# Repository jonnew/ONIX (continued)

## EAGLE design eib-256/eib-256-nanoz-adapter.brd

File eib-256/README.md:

# eib-256
256-channel electrode interface board (EIB) with electrical and optical
stimulation. Designed for large animal (e.g. rat) tetrode electrophysiology.
Compatible with [headstage-256](../headstage-256/) and large shuttle-drives.

## Gerber Files
{% include gerber_layers.md %}

## Bill of Materials
The BOM is located on [this google
sheet](https://docs.google.com/spreadsheets/d/1F-KWcdvH_63iXjZf0cgCfDiFX6XXW3qw6rlR8DZrFpQ/edit#gid=1934583654).

## Pinout
The EIB pinout (ADC input mapping, stimulation connections, etc) is located on [this google sheet](https://docs.google.com/spreadsheets/d/11wRDYOqHN5lPb03yUdfXfK0zvaDYsVetplaNK-R90Gg/edit#gid=0)

## Tetrode Connectorization
This EIB uses Neuralynx ["small" gold pins](https://neuralynx.com/hardware/small-eib-pins) to attach tetrode wires. Usage instructions are provided in the [Neuralynx EIB pin Manual](https://neuralynx.com/documents/EIB%20Pins%20Manual.pdf).

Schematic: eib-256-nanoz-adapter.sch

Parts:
A: DF40HEAD; DF40-70REC
B: DF40HEAD; DF40-70REC
C: DF40HEAD; DF40-70REC
C1, C2, C5, C6, C10, C12, C13, C15, C20, C22, C23, C25, C29, C30, C33, C34: 1uF; 0603
C3, C4, C7, C8, C9, C11, C14, C16, C19, C21, C24, C26, C27, C28, C31, C32: 0.1uF; 0402
C17, C18: 10uF; 1210-POL
D: DF40HEAD; DF40-70REC
D1, D2: UDZ10B-7; SOD-323; PARTNO UDZ10B-7
D3, D4: LED_0603; LED-0603
J1, J2, J3, J4, J5: JP3E_SMD; JP3_SMD
J6: SCREW4
J7, J8: PINHD-4X10_MOLC-THRU; MOLC-110-11-S-Q
Q1: DMN3404L; SOT23-GSD; PARTNO DMN3404L-7
Q2: DMP3056L; SOT23-GSD; PARTNO DMP3056L-7
R1, R2, R5, R6: 1k; 0603
R3, R4: 10k; 0603
S1: 219-2MSTR; SMS-002
U1, U2, U3, U4, U5, U6, U7, U8, U9, U10, U11, U12, U13, U14, U15, U16, U17, U18, U19, U20, U21, U22, U23, U24, U25, U26, U27, U28, U29, U30, U31, U32: DG4052E_MQFN; MQFN16-1.8X2.6

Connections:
A: J1.2, R3.1, U1.8 (A), U2.8 (A), U3.8 (A), U4.8 (A), U5.8 (A), U6.8 (A), U7.8 (A), U8.8 (A), U9.8 (A), U10.8 (A), U11.8 (A), U12.8 (A), U13.8 (A), U14.8 (A), U15.8 (A), U16.8 (A), U17.8 (A), U18.8 (A), U19.8 (A), U20.8 (A), U21.8 (A), U22.8 (A), U23.8 (A), U24.8 (A), U25.8 (A), U26.8 (A), U27.8 (A), U28.8 (A), U29.8 (A), U30.8 (A), U31.8 (A), U32.8 (A)
B: J2.2, R4.1, U1.7 (B), U2.7 (B), U3.7 (B), U4.7 (B), U5.7 (B), U6.7 (B), U7.7 (B), U8.7 (B), U9.7 (B), U10.7 (B), U11.7 (B), U12.7 (B), U13.7 (B), U14.7 (B), U15.7 (B), U16.7 (B), U17.7 (B), U18.7 (B), U19.7 (B), U20.7 (B), U21.7 (B), U22.7 (B), U23.7 (B), U24.7 (B), U25.7 (B), U26.7 (B), U27.7 (B), U28.7 (B), U29.7 (B), U30.7 (B), U31.7 (B), U32.7 (B)
GND: C1.2, C2.2, C3.2, C4.2, C5.2, C6.2, C7.2, C8.2, C9.2, C10.2, C11.2, C12.2, C13.2, C14.2, C15.2, C16.2, C17.-, C18.+, C19.2, C20.2, C21.2, C22.2, C23.2, C24.2, C25.2, C26.2, C27.2, C28.2, C29.2, C30.2, C31.2, C32.2, C33.2, C34.2, D3.C, D4.A, J3.1, J3.2, J6.3, R1.1, R2.2, S1.1, S1.2, U1.4 (!EN), U1.6 (GND), U2.4 (!EN), U2.6 (GND), U3.4 (!EN), U3.6 (GND), U4.4 (!EN), U4.6 (GND), U5.4 (!EN), U5.6 (GND), U6.4 (!EN), U6.6 (GND), U7.4 (!EN), U7.6 (GND), U8.4 (!EN), U8.6 (GND), U9.4 (!EN), U9.6 (GND), U10.4 (!EN), U10.6 (GND), U11.4 (!EN), U11.6 (GND), U12.4 (!EN), U12.6 (GND), U14.4 (!EN), U14.6 (GND), U15.4 (!EN), U15.6 (GND), U16.4 (!EN), U16.6 (GND), U17.4 (!EN), U17.6 (GND), U18.4 (!EN), U18.6 (GND), U19.4 (!EN), U19.6 (GND), U20.4 (!EN), U20.6 (GND), U21.4 (!EN), U21.6 (GND), U22.4 (!EN), U22.6 (GND), U24.4 (!EN), U24.6 (GND), U25.4 (!EN), U25.6 (GND), U26.4 (!EN), U26.6 (GND), U27.4 (!EN), U27.6 (GND), U28.4 (!EN), U28.6 (GND), U29.4 (!EN), U29.6 (GND), U30.4 (!EN), U30.6 (GND), U32.4 (!EN), U32.6 (GND)
GND1: U13.6 (GND)
GND2: U23.6 (GND)
GND4: U31.6 (GND)
GND_HEAD: J3.3, J7.B4 (17)
GPIO0_HEAD: J1.1, J7.C3 (3)
GPIO1_HEAD: J2.1, J7.C4 (4)
GPIO2_HEAD: J8.C3 (3)
GPIO3_HEAD: J8.C4 (4)
unnamed: C.2, U1.9 (X3)
unnamed: C.3, U1.10 (X0)
unnamed: C.4, U1.12 (X1)
unnamed: C.5, U1.13 (X2)
unnamed: C.6, U1.15 (Y0)
unnamed: C.7, U1.16 (Y2)
unnamed: C.8, U1.2 (Y3)
unnamed: C.9, U1.3 (Y1)
unnamed: C.10, U2.9 (X3)
unnamed: C.11, U2.10 (X0)
unnamed: C.12, U2.12 (X1)
unnamed: C.13, U2.13 (X2)
unnamed: C.14, U2.15 (Y0)
unnamed: C.15, U2.16 (Y2)
unnamed: C.16, U2.2 (Y3)
unnamed: C.17, U2.3 (Y1)
unnamed: C.18, U3.9 (X3)
unnamed: C.19, U3.10 (X0)
unnamed: C.20, U3.12 (X1)
unnamed: C.21, U3.13 (X2)
unnamed: C.22, U3.15 (Y0)
unnamed: C.23, U3.16 (Y2)
unnamed: C.24, U3.2 (Y3)
unnamed: C.25, U3.3 (Y1)
unnamed: C.26, U4.9 (X3)
unnamed: C.27, U4.10 (X0)
unnamed: C.28, U4.12 (X1)
unnamed: C.29, U4.13 (X2)
unnamed: C.30, U4.15 (Y0)
unnamed: C.31, U4.16 (Y2)
unnamed: C.32, U4.2 (Y3)
unnamed: C.33, U4.3 (Y1)
unnamed: C.41, U8.13 (X2)
unnamed: C.42, U8.12 (X1)
unnamed: C.43, U8.10 (X0)
unnamed: C.44, U8.9 (X3)
unnamed: C.45, U7.3 (Y1)
unnamed: C.46, U7.2 (Y3)
unnamed: C.47, U7.16 (Y2)
unnamed: C.48, U7.15 (Y0)
unnamed: C.49, U7.13 (X2)
unnamed: C.37, U8.3 (Y1)
unnamed: C.38, U8.2 (Y3)
unnamed: C.39, U8.16 (Y2)
unnamed: C.40, U8.15 (Y0)
unnamed: C.50, U7.12 (X1)
unnamed: C.51, U7.10 (X0)
unnamed: C.52, U7.9 (X3)
unnamed: C.53, U6.3 (Y1)
unnamed: C.54, U6.2 (Y3)
unnamed: C.55, U6.16 (Y2)
unnamed: C.56, U6.15 (Y0)
unnamed: C.57, U6.13 (X2)
unnamed: C.58, U6.12 (X1)
unnamed: C.59, U6.10 (X0)
unnamed: C.60, U6.9 (X3)
unnamed: C.61, U5.3 (Y1)
unnamed: C.62, U5.2 (Y3)
unnamed: C.63, U5.16 (Y2)
unnamed: C.64, U5.15 (Y0)
unnamed: C.65, U5.13 (X2)
unnamed: C.66, U5.12 (X1)
unnamed: C.67, U5.10 (X0)
unnamed: C.68, U5.9 (X3)
unnamed: D3.A, R5.1
unnamed: D1.A, Q2.G, R1.2
unnamed: D4.C, R6.2
unnamed: D2.C, Q1.G, R2.1
unnamed: J1.3, S1.4
unnamed: J2.3, S1.3
REF: J6.4, J7.B1 (20), J7.C1 (1), J7.C2 (2), J8.B1 (20), J8.C1 (1), J8.C2 (2)
TT00: J8.A1 (1), U24.11 (X)
TT01: J8.A2 (2), U24.1 (Y)
TT02: J8.A3 (3), U23.11 (X)
TT03: J8.A4 (4), U23.1 (Y)
TT04: J8.A5 (5), U21.11 (X)
TT05: J8.B5 (16), U21.1 (Y)
TT06: J8.A6 (6), U19.11 (X)
TT07: J8.B6 (15), U19.1 (Y)
TT08: J8.A10 (10), U11.11 (X)
TT09: J8.B10 (11), U11.1 (Y)
TT10: J8.A9 (9), U13.11 (X)
TT11: J8.B9 (12), U13.1 (Y)
TT12: J8.A8 (8), U15.11 (X)
TT13: J8.B8 (13), U15.1 (Y)
TT14: J8.A7 (7), U17.11 (X)
TT15: J8.B7 (14), U17.1 (Y)
TT16: J8.C10 (10), U1.11 (X)
TT17: J8.D10 (11), U1.1 (Y)
TT18: J8.C9 (9), U2.11 (X)
TT19: J8.D9 (12), U2.1 (Y)
TT20: J8.C8 (8), U3.11 (X)
TT21: J8.D8 (13), U3.1 (Y)
TT22: J8.C7 (7), U4.11 (X)
TT23: J8.D7 (14), U4.1 (Y)
TT24: J8.D2 (19), U8.11 (X)
TT25: J8.D1 (20), U8.1 (Y)
TT26: J8.D4 (17), U7.11 (X)
TT27: J8.D3 (18), U7.1 (Y)
TT28: J8.C5 (5), U6.11 (X)
TT29: J8.D5 (16), U6.1 (Y)
TT30: J8.C6 (6), U5.11 (X)
TT31: J8.D6 (15), U5.1 (Y)
TT32: J7.C10 (10), U9.11 (X)
TT33: J7.D10 (11), U9.1 (Y)
TT34: J7.C9 (9), U10.11 (X)
TT35: J7.D9 (12), U10.1 (Y)
TT36: J7.C8 (8), U12.11 (X)
TT37: J7.D8 (13), U12.1 (Y)
TT38: J7.C7 (7), U14.11 (X)
TT39: J7.D7 (14), U14.1 (Y)
TT40: J7.D2 (19), U22.11 (X)
TT41: J7.D1 (20), U22.1 (Y)
TT42: J7.D4 (17), U20.11 (X)
TT43: J7.D3 (18), U20.1 (Y)
TT44: J7.C5 (5), U18.11 (X)
TT45: J7.D5 (16), U18.1 (Y)
TT46: J7.C6 (6), U16.11 (X)
TT47: J7.D6 (15), U16.1 (Y)
TT48: J7.A1 (1), U32.11 (X)
TT49: J7.A2 (2), U32.1 (Y)
TT50: J7.A3 (3), U31.11 (X)
TT51: J7.A4 (4), U31.1 (Y)
TT52: J7.A5 (5), U30.11 (X)
TT53: J7.B5 (16), U30.1 (Y)
TT54: J7.A6 (6), U29.11 (X)
TT55: J7.B6 (15), U29.1 (Y)
TT56: J7.A10 (10), U25.11 (X)
TT57: J7.B10 (11), U25.1 (Y)
TT58: J7.A9 (9), U26.11 (X)
TT59: J7.B9 (12), U26.1 (Y)
TT60: J7.A8 (8), U27.11 (X)
TT61: J7.B8 (13), U27.1 (Y)
TT62: J7.A7 (7), U28.11 (X)
TT63: J7.B7 (14), U28.1 (Y)
VCC: C1.1, C2.1, C3.1, C4.1, C9.1, C10.1, C15.1, C16.1, C17.+, C19.1, C20.1, C25.1, C26.1, C31.1, C32.1, C33.1, C34.1, D1.C, Q2.S, R3.2, R4.2, R5.2, U1.14 (V+), U2.14 (V+), U3.14 (V+), U4.14 (V+), U5.14 (V+), U6.14 (V+), U7.14 (V+), U8.14 (V+), U9.14 (V+), U10.14 (V+), U11.14 (V+), U12.14 (V+), U13.14 (V+), U14.14 (V+), U15.14 (V+), U16.14 (V+), U17.14 (V+), U18.14 (V+), U19.14 (V+), U20.14 (V+), U21.14 (V+), U22.14 (V+), U23.14 (V+), U24.14 (V+), U25.14 (V+), U26.14 (V+), U27.14 (V+), U28.14 (V+), U29.14 (V+), U30.14 (V+), U31.14 (V+), U32.14 (V+)
VCC_HEAD: J5.3, J7.B2 (19)
VCC_LOCAL: J5.1, J6.1
VCC_PRE: J5.2, Q2.D
VSS: C5.1, C6.1, C7.1, C8.1, C11.1, C12.1, C13.1, C14.1, C18.-, C21.1, C22.1, C23.1, C24.1, C27.1, C28.1, C29.1, C30.1, D2.A, Q1.S, R6.1, U1.5 (V-), U2.5 (V-), U3.5 (V-), U4.5 (V-), U5.5 (V-), U6.5 (V-), U7.5 (V-), U8.5 (V-), U9.5 (V-), U10.5 (V-), U11.5 (V-), U12.5 (V-), U13.5 (V-), U14.5 (V-), U15.5 (V-), U16.5 (V-), U17.5 (V-), U18.5 (V-), U19.5 (V-), U20.5 (V-), U21.5 (V-), U22.5 (V-), U23.5 (V-), U24.5 (V-), U25.5 (V-), U26.5 (V-), U27.5 (V-), U28.5 (V-), U29.5 (V-), U30.5 (V-), U31.5 (V-), U32.5 (V-)
VSS_HEAD: J4.3, J7.B3 (18)
VSS_LOCAL: J4.1, J6.2
VSS_PRE: J4.2, Q1.D

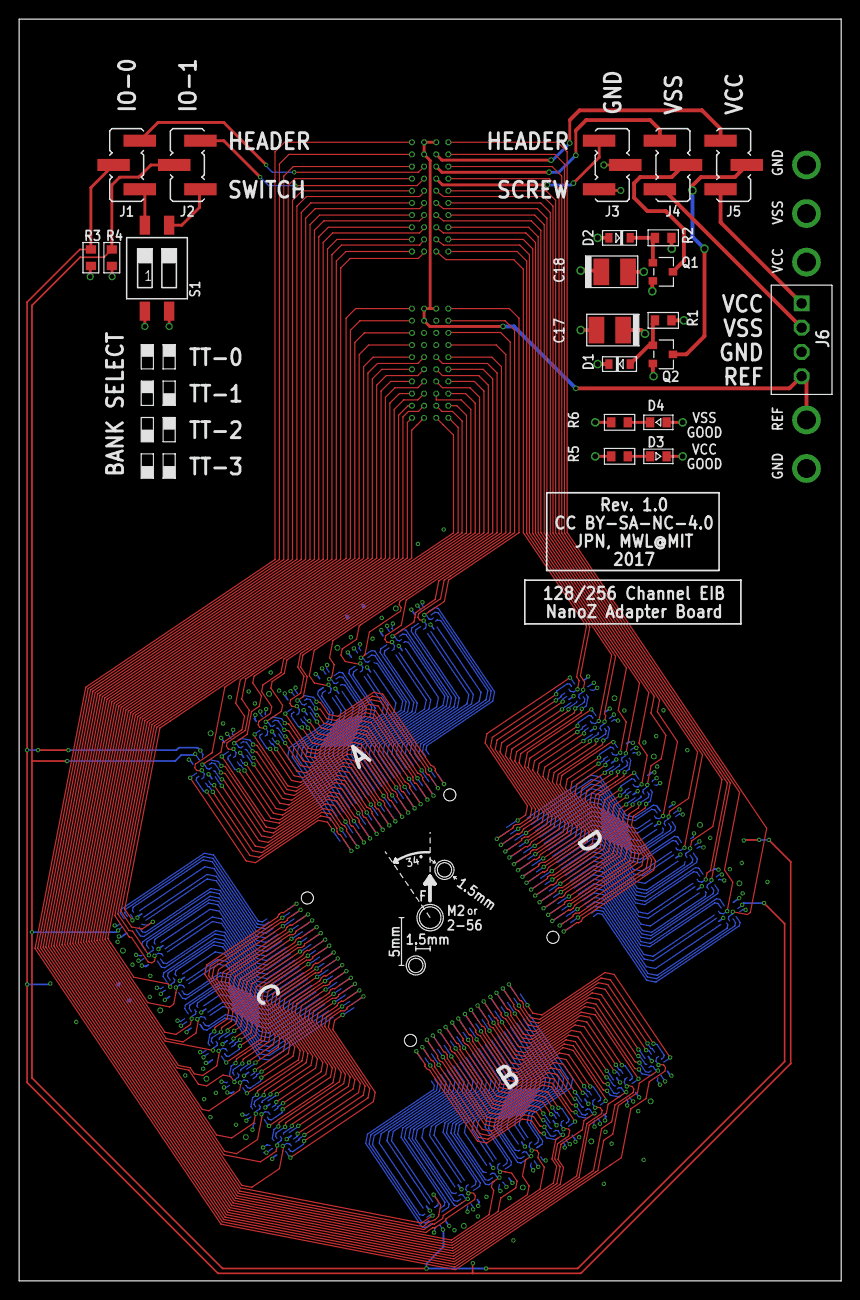
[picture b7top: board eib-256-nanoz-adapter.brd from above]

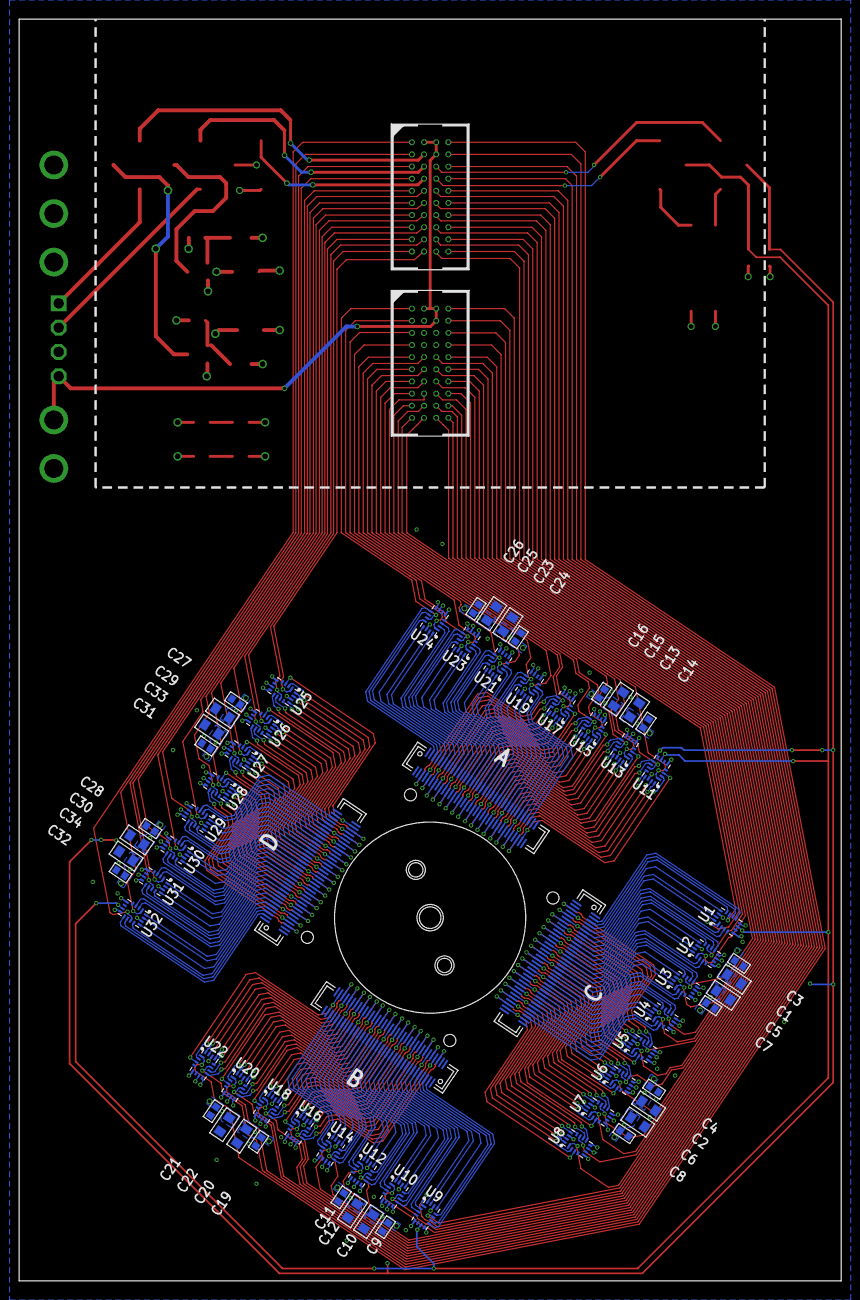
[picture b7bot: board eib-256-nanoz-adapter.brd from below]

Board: 4 copper layers, 86.0 x 132.0 mm, 92 parts (70 on the bottom side), 149 nets.

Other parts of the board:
U$1: EIB_MOUNT_A

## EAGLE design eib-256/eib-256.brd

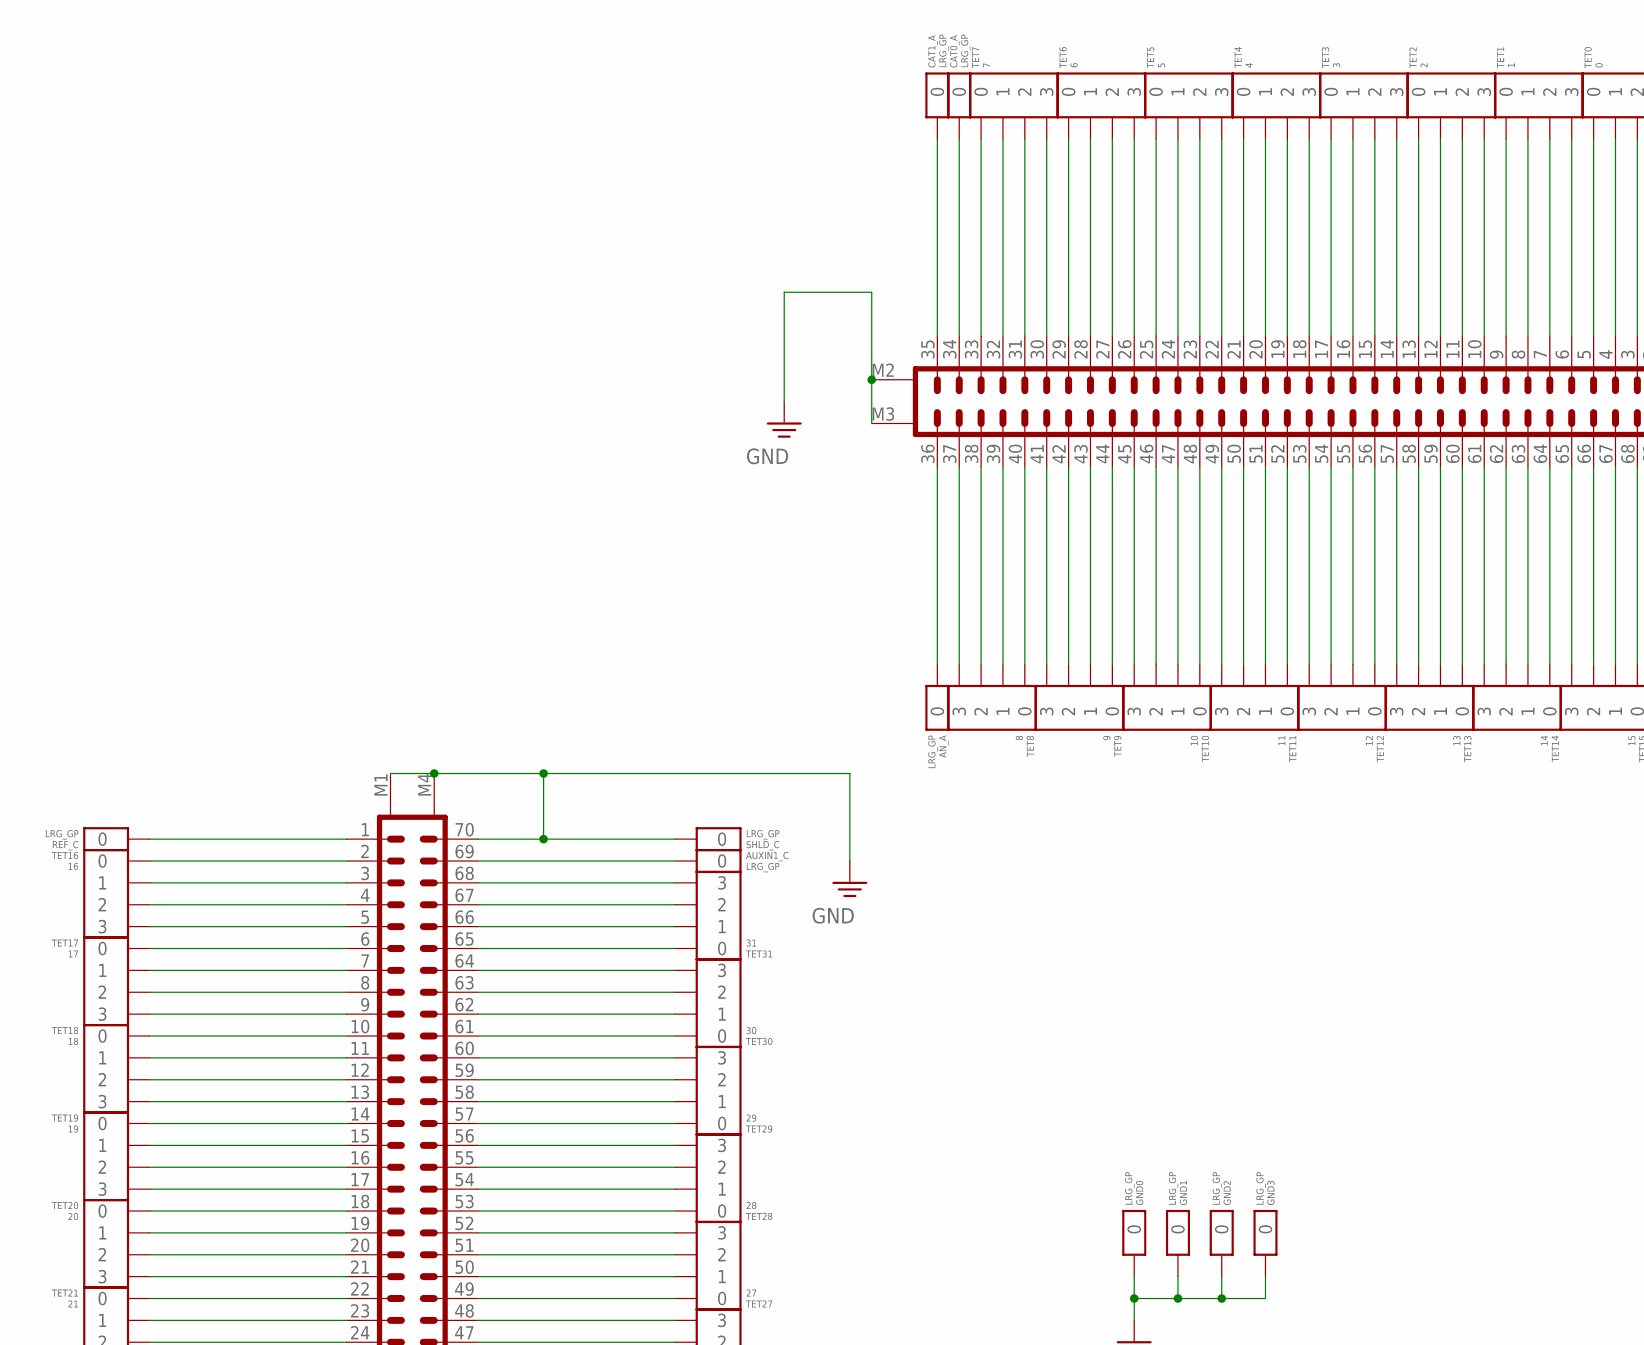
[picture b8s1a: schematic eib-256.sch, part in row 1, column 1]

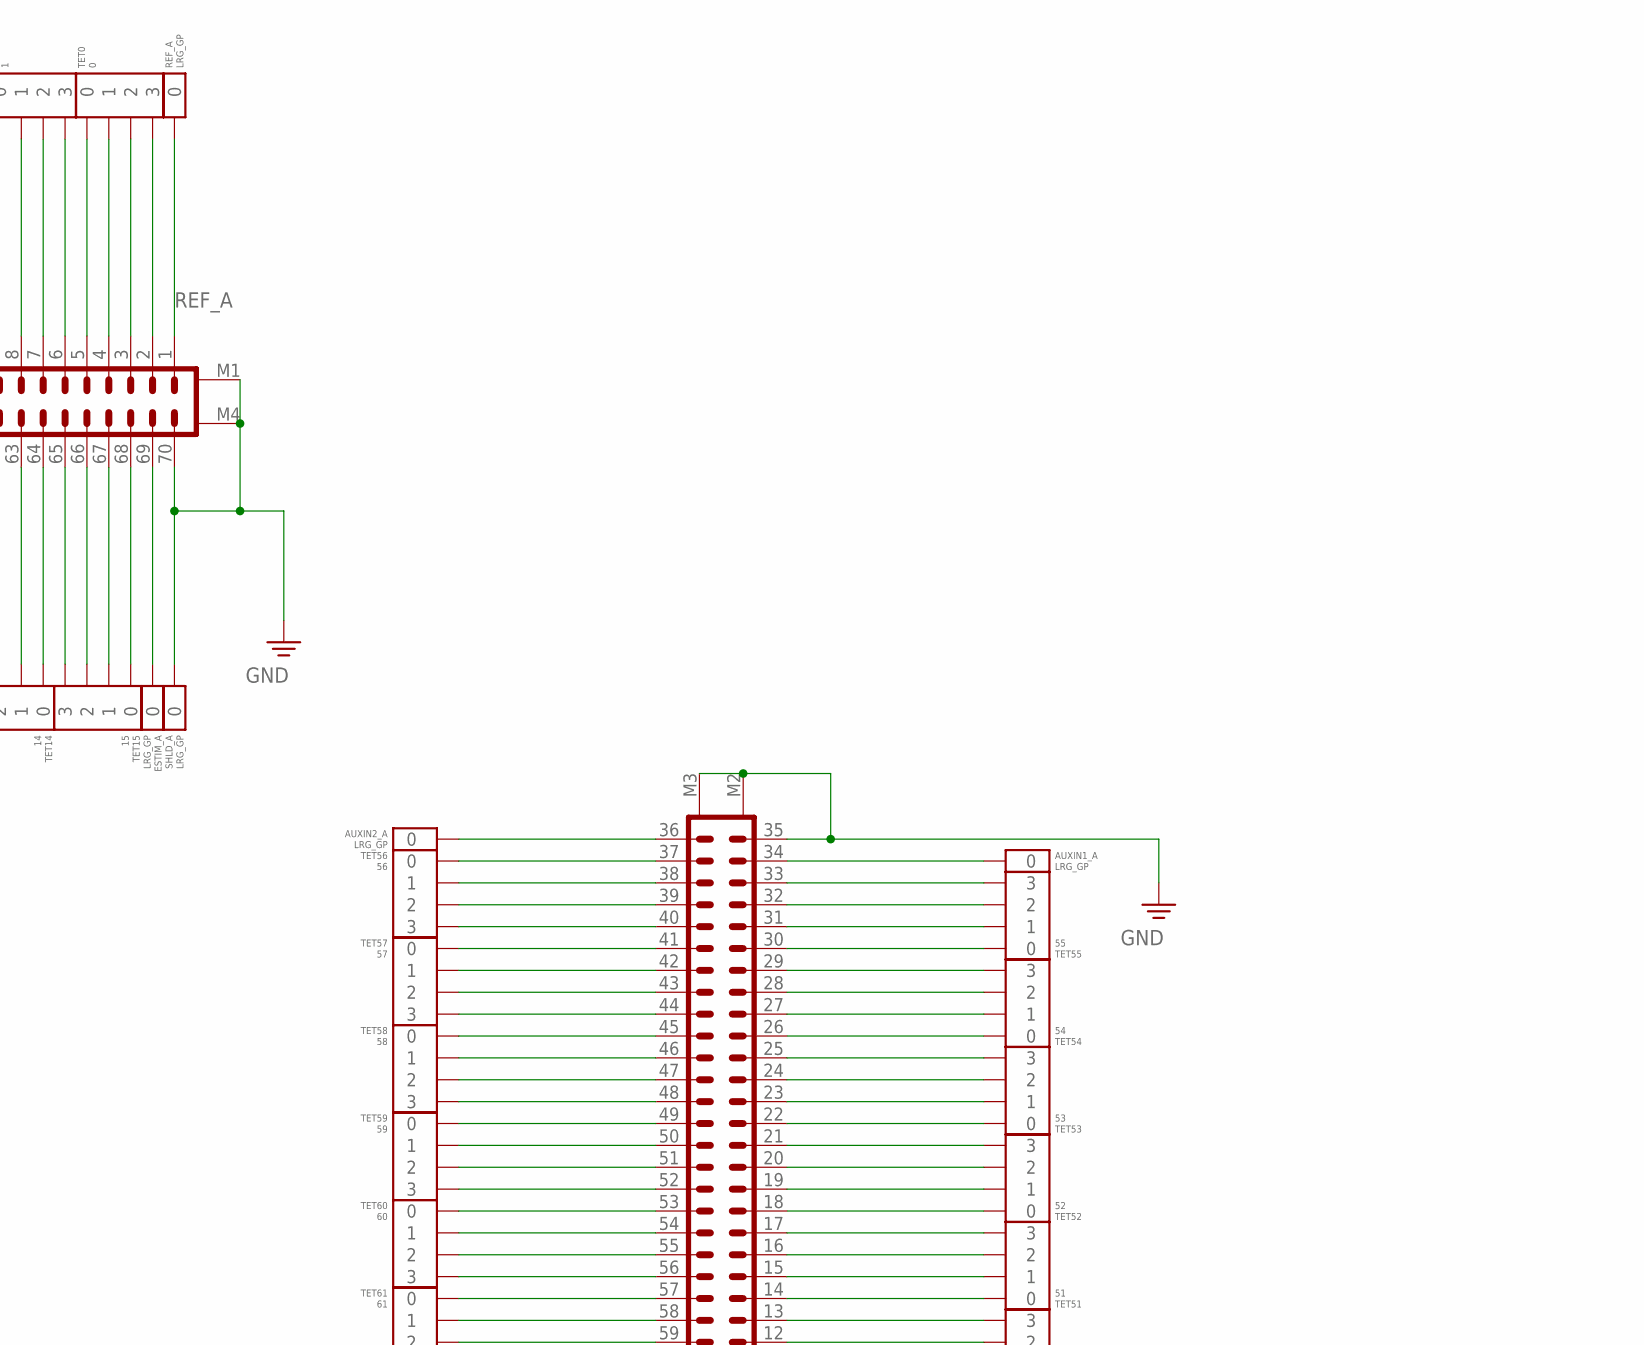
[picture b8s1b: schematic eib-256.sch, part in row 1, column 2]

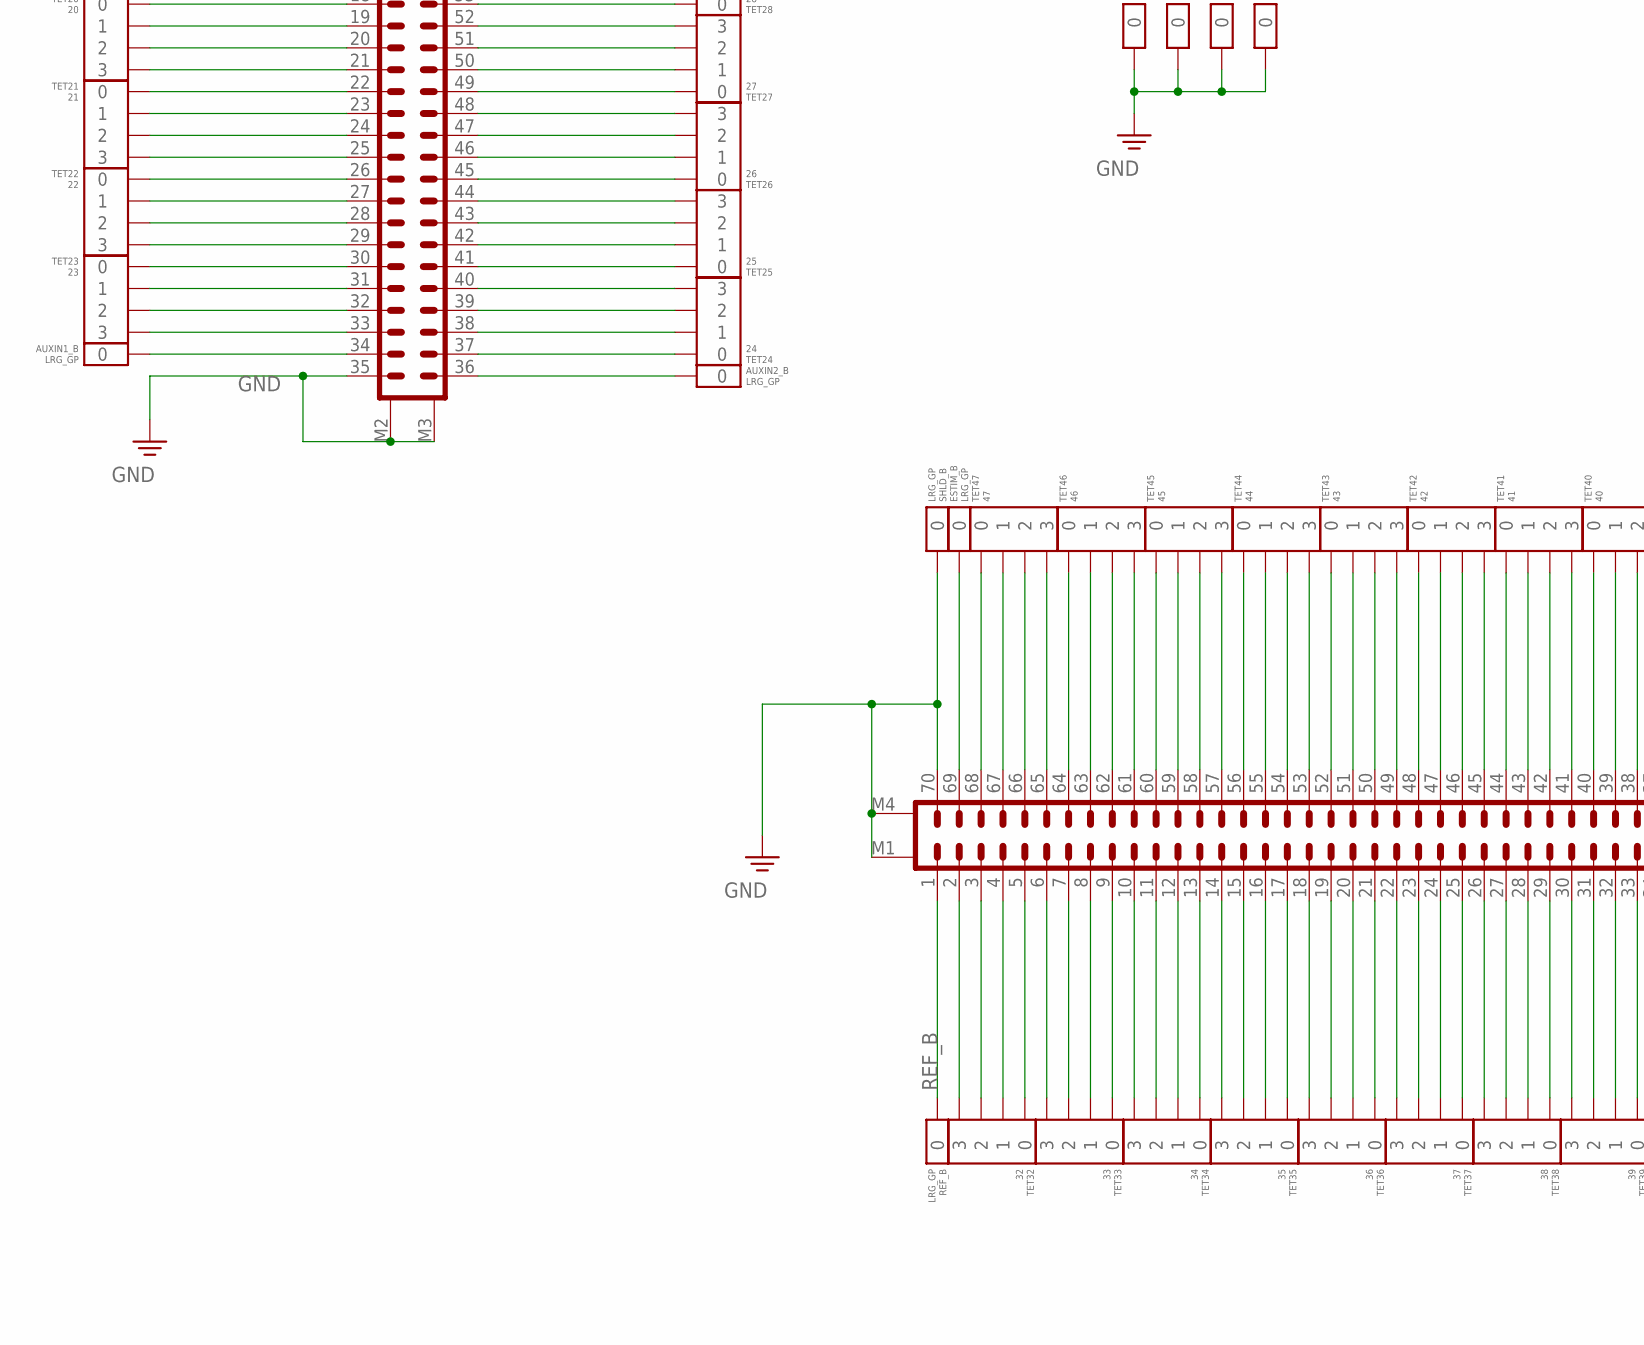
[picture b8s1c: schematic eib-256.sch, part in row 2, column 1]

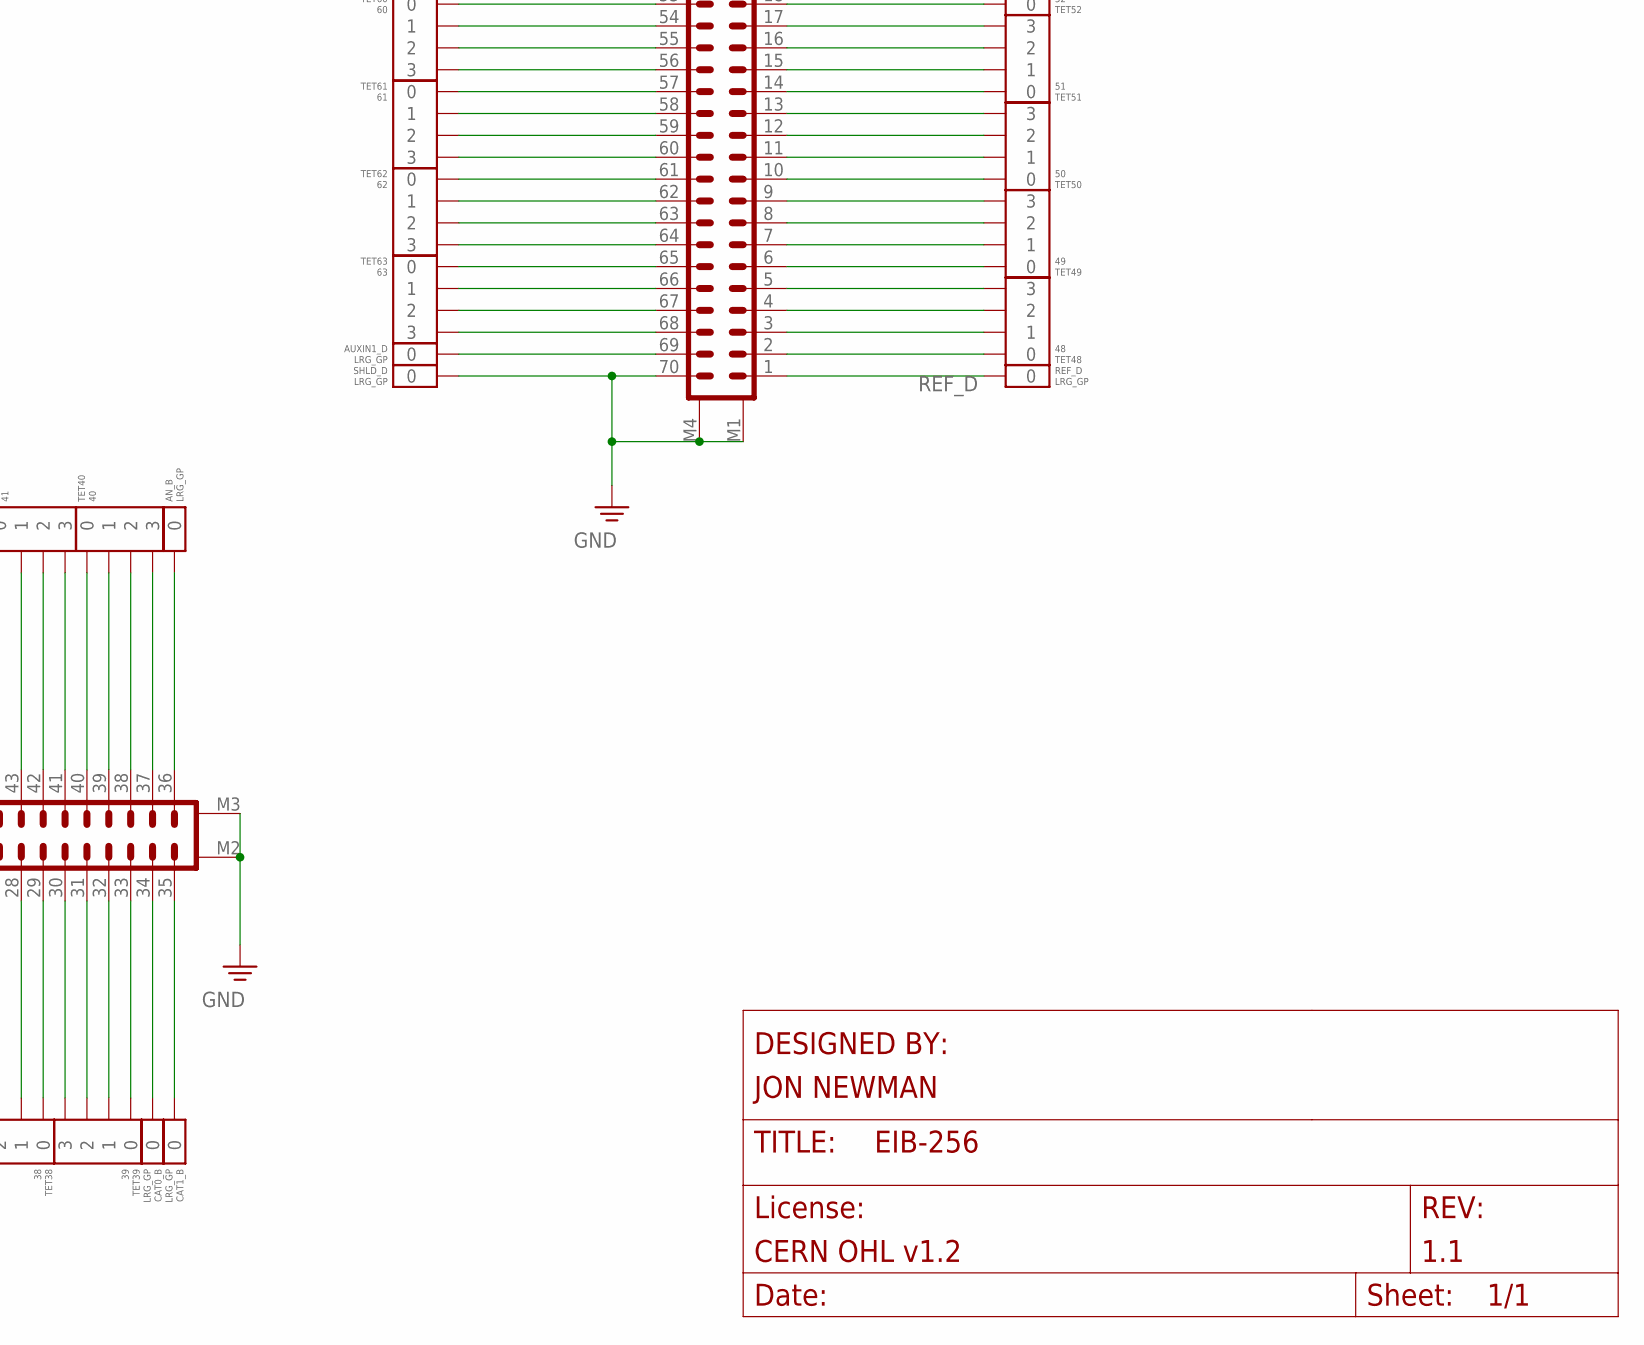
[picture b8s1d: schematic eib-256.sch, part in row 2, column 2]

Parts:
A: DF40HEAD; DF40-70HEAD
AN_A: LRG_GP; GOLDPIN_0.5ID_0.7OD
AN_B: LRG_GP; GOLDPIN_0.5ID_0.7OD
AUXIN1_A, AUXIN1_B, AUXIN1_C, AUXIN1_D, AUXIN2_A, AUXIN2_B: LRG_GP; GOLDPIN_0.5ID_0.7OD
B: DF40HEAD; DF40-70HEAD
C: DF40HEAD; DF40-70HEAD
CAT0_A, CAT0_B, CAT1_A, CAT1_B: LRG_GP; GOLDPIN_0.5ID_0.7OD
D: DF40HEAD; DF40-70HEAD
ESTIM_A: LRG_GP; GOLDPIN_0.5ID_0.7OD
ESTIM_B: LRG_GP; GOLDPIN_0.5ID_0.7OD
GND0, GND1, GND2, GND3: LRG_GP; GOLDPIN_0.5ID_0.7OD
REF_A: LRG_GP; GOLDPIN_0.5ID_0.7OD
REF_B: LRG_GP; GOLDPIN_0.5ID_0.7OD
REF_C: LRG_GP; GOLDPIN_0.5ID_0.7OD
REF_D: LRG_GP; GOLDPIN_0.5ID_0.7OD
SHLD_A: LRG_GP; GOLDPIN_0.5ID_0.7OD
SHLD_B: LRG_GP; GOLDPIN_0.5ID_0.7OD
SHLD_C: LRG_GP; GOLDPIN_0.5ID_0.7OD
SHLD_D: LRG_GP; GOLDPIN_0.5ID_0.7OD
TET0: 0; TETRODE_0.3ID_LINEAR
TET1: 1; TETRODE_0.3ID_LINEAR
TET2: 2; TETRODE_0.3ID_LINEAR
TET3: 3; TETRODE_0.3ID_LINEAR
TET4: 4; TETRODE_0.3ID_LINEAR
TET5: 5; TETRODE_0.3ID_LINEAR
TET6: 6; TETRODE_0.3ID_LINEAR
TET7: 7; TETRODE_0.3ID_LINEAR
TET8: 8; TETRODE_0.3ID_LINEAR
TET9: 9; TETRODE_0.3ID_LINEAR
TET10: 10; TETRODE_0.3ID_LINEAR
TET11: 11; TETRODE_0.3ID_LINEAR
TET12: 12; TETRODE_0.3ID_LINEAR
TET13: 13; TETRODE_0.3ID_LINEAR
TET14: 14; TETRODE_0.3ID_LINEAR
TET15: 15; TETRODE_0.3ID_LINEAR
TET16: 16; TETRODE_0.3ID_LINEAR
TET17: 17; TETRODE_0.3ID_LINEAR
TET18: 18; TETRODE_0.3ID_LINEAR
TET19: 19; TETRODE_0.3ID_LINEAR
TET20: 20; TETRODE_0.3ID_LINEAR
TET21: 21; TETRODE_0.3ID_LINEAR
TET22: 22; TETRODE_0.3ID_LINEAR
TET23: 23; TETRODE_0.3ID_LINEAR
TET24: 24; TETRODE_0.3ID_LINEAR
TET25: 25; TETRODE_0.3ID_LINEAR
TET26: 26; TETRODE_0.3ID_LINEAR
TET27: 27; TETRODE_0.3ID_LINEAR
TET28: 28; TETRODE_0.3ID_LINEAR
TET29: 29; TETRODE_0.3ID_LINEAR
TET30: 30; TETRODE_0.3ID_LINEAR
TET31: 31; TETRODE_0.3ID_LINEAR
TET32: 32; TETRODE_0.3ID_LINEAR
TET33: 33; TETRODE_0.3ID_LINEAR
TET34: 34; TETRODE_0.3ID_LINEAR
TET35: 35; TETRODE_0.3ID_LINEAR
TET36: 36; TETRODE_0.3ID_LINEAR
TET37: 37; TETRODE_0.3ID_LINEAR
TET38: 38; TETRODE_0.3ID_LINEAR
TET39: 39; TETRODE_0.3ID_LINEAR
TET40: 40; TETRODE_0.3ID_LINEAR
TET41: 41; TETRODE_0.3ID_LINEAR
TET42: 42; TETRODE_0.3ID_LINEAR
TET43: 43; TETRODE_0.3ID_LINEAR
TET44: 44; TETRODE_0.3ID_LINEAR
TET45: 45; TETRODE_0.3ID_LINEAR
TET46: 46; TETRODE_0.3ID_LINEAR
TET47: 47; TETRODE_0.3ID_LINEAR
TET48: 48; TETRODE_0.3ID_LINEAR
TET49: 49; TETRODE_0.3ID_LINEAR
TET50: 50; TETRODE_0.3ID_LINEAR
TET51: 51; TETRODE_0.3ID_LINEAR
TET52: 52; TETRODE_0.3ID_LINEAR
TET53: 53; TETRODE_0.3ID_LINEAR
TET54: 54; TETRODE_0.3ID_LINEAR
TET55: 55; TETRODE_0.3ID_LINEAR
TET56: 56; TETRODE_0.3ID_LINEAR
TET57: 57; TETRODE_0.3ID_LINEAR
TET58: 58; TETRODE_0.3ID_LINEAR
TET59: 59; TETRODE_0.3ID_LINEAR
TET60: 60; TETRODE_0.3ID_LINEAR
TET61: 61; TETRODE_0.3ID_LINEAR
TET62: 62; TETRODE_0.3ID_LINEAR
TET63: 63; TETRODE_0.3ID_LINEAR

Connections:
AN_A: A.36, AN_A.P$1
AN_B: AN_B.P$1, B.36
AUXIN1_A: AUXIN1_A.P$1, D.34
AUXIN1_B: AUXIN1_B.P$1, C.34
AUXIN1_C: AUXIN1_C.P$1, C.69
AUXIN1_D: AUXIN1_D.P$1, D.69
AUXIN2_A: AUXIN2_A.P$1, D.36
AUXIN2_B: AUXIN2_B.P$1, C.36
CAT0_A: A.34, CAT0_A.P$1
CAT0_B: B.34, CAT0_B.P$1
CAT1_A: A.35, CAT1_A.P$1
CAT1_B: B.35, CAT1_B.P$1
ESTIM_A: A.69, ESTIM_A.P$1
ESTIM_B: B.69, ESTIM_B.P$1
GND: A.70, A.M1, A.M2, A.M3, A.M4, B.70, B.M1, B.M2, B.M3, B.M4, C.35, C.70, C.M1, C.M2, C.M3, C.M4, D.35, D.70, D.M1, D.M2, D.M3, D.M4, GND0.P$1, GND1.P$1, GND2.P$1, GND3.P$1, SHLD_A.P$1, SHLD_B.P$1, SHLD_C.P$1, SHLD_D.P$1
unnamed: D.2, TET48.0
unnamed: D.3, TET48.1
unnamed: D.4, TET48.2
unnamed: D.5, TET48.3
unnamed: D.6, TET49.0
unnamed: D.7, TET49.1
unnamed: D.8, TET49.2
unnamed: D.9, TET49.3
unnamed: D.10, TET50.0
unnamed: D.11, TET50.1
unnamed: D.12, TET50.2
unnamed: D.13, TET50.3
unnamed: D.14, TET51.0
unnamed: D.15, TET51.1
unnamed: D.16, TET51.2
unnamed: D.17, TET51.3
unnamed: D.18, TET52.0
unnamed: D.19, TET52.1
unnamed: D.20, TET52.2
unnamed: D.21, TET52.3
unnamed: D.22, TET53.0
unnamed: D.23, TET53.1
unnamed: D.24, TET53.2
unnamed: D.25, TET53.3
unnamed: D.26, TET54.0
unnamed: D.27, TET54.1
unnamed: D.28, TET54.2
unnamed: D.29, TET54.3
unnamed: D.30, TET55.0
unnamed: D.31, TET55.1
unnamed: D.32, TET55.2
unnamed: D.42, TET57.1
unnamed: D.43, TET57.2
unnamed: D.44, TET57.3
unnamed: D.45, TET58.0
unnamed: D.46, TET58.1
unnamed: D.47, TET58.2
unnamed: D.48, TET58.3
unnamed: D.49, TET59.0
unnamed: D.50, TET59.1
unnamed: D.51, TET59.2
unnamed: D.52, TET59.3
unnamed: D.53, TET60.0
unnamed: D.54, TET60.1
unnamed: D.55, TET60.2
unnamed: D.56, TET60.3
unnamed: D.57, TET61.0
unnamed: D.58, TET61.1
unnamed: D.59, TET61.2
unnamed: D.60, TET61.3
unnamed: D.61, TET62.0
unnamed: D.62, TET62.1
unnamed: D.63, TET62.2
unnamed: D.64, TET62.3
unnamed: D.65, TET63.0
unnamed: D.66, TET63.1
unnamed: D.67, TET63.2
unnamed: D.68, TET63.3
unnamed: D.41, TET57.0
unnamed: D.40, TET56.3
unnamed: D.39, TET56.2
unnamed: D.38, TET56.1
unnamed: D.33, TET55.3
unnamed: D.37, TET56.0
unnamed: C.3, TET16.1
unnamed: C.2, TET16.0
unnamed: C.32, TET23.2
unnamed: C.33, TET23.3
unnamed: C.28, TET22.2
unnamed: C.29, TET22.3
unnamed: C.24, TET21.2
unnamed: C.25, TET21.3
unnamed: C.20, TET20.2
unnamed: C.21, TET20.3
unnamed: C.16, TET19.2
unnamed: C.17, TET19.3
unnamed: C.12, TET18.2
unnamed: C.13, TET18.3
unnamed: C.8, TET17.2
unnamed: C.9, TET17.3
unnamed: C.66, TET31.1
unnamed: C.65, TET31.0
unnamed: C.62, TET30.1
unnamed: C.64, TET30.3
unnamed: C.58, TET29.1
unnamed: C.57, TET29.0
unnamed: C.54, TET28.1
unnamed: C.53, TET28.0
unnamed: C.49, TET27.0
unnamed: C.50, TET27.1
unnamed: C.46, TET26.1
unnamed: C.45, TET26.0
unnamed: C.42, TET25.1
unnamed: C.41, TET25.0
unnamed: C.38, TET24.1
unnamed: C.37, TET24.0
unnamed: B.33, TET39.0
unnamed: B.32, TET39.1
unnamed: B.31, TET39.2
unnamed: B.30, TET39.3
unnamed: B.29, TET38.0
unnamed: B.28, TET38.1
unnamed: A.33, TET7.0
unnamed: A.32, TET7.1
unnamed: A.31, TET7.2
unnamed: A.30, TET7.3
unnamed: A.29, TET6.0
unnamed: A.28, TET6.1
unnamed: A.27, TET6.2
unnamed: A.26, TET6.3
unnamed: A.25, TET5.0
unnamed: A.24, TET5.1
unnamed: A.23, TET5.2
unnamed: A.22, TET5.3
unnamed: A.21, TET4.0
unnamed: A.20, TET4.1
unnamed: A.19, TET4.2
unnamed: A.18, TET4.3
unnamed: A.17, TET3.0
unnamed: A.16, TET3.1
unnamed: A.15, TET3.2
unnamed: A.14, TET3.3
unnamed: A.13, TET2.0
unnamed: A.12, TET2.1
unnamed: A.11, TET2.2
unnamed: A.10, TET2.3
unnamed: A.9, TET1.0
unnamed: A.8, TET1.1
unnamed: A.7, TET1.2
unnamed: A.6, TET1.3
unnamed: A.5, TET0.0
unnamed: A.4, TET0.1
unnamed: A.3, TET0.2
unnamed: A.2, TET0.3
unnamed: A.38, TET8.2
unnamed: A.39, TET8.1
unnamed: A.40, TET8.0
unnamed: A.41, TET9.3
unnamed: A.42, TET9.2
unnamed: A.43, TET9.1
unnamed: A.44, TET9.0
unnamed: A.45, TET10.3
unnamed: A.46, TET10.2
unnamed: A.47, TET10.1
unnamed: A.48, TET10.0
unnamed: A.49, TET11.3
unnamed: A.50, TET11.2
unnamed: A.51, TET11.1
unnamed: A.52, TET11.0
unnamed: A.53, TET12.3
unnamed: A.54, TET12.2
unnamed: A.55, TET12.1
unnamed: A.56, TET12.0
unnamed: A.57, TET13.3
unnamed: A.58, TET13.2
unnamed: A.59, TET13.1
unnamed: A.60, TET13.0
unnamed: A.61, TET14.3
unnamed: A.62, TET14.2
unnamed: A.63, TET14.1
unnamed: A.64, TET14.0
unnamed: A.65, TET15.3
unnamed: A.66, TET15.2
unnamed: A.67, TET15.1
unnamed: A.68, TET15.0
unnamed: B.27, TET38.2
unnamed: B.26, TET38.3
unnamed: B.25, TET37.0
unnamed: B.24, TET37.1
unnamed: B.23, TET37.2
unnamed: B.22, TET37.3
unnamed: B.21, TET36.0
unnamed: B.20, TET36.1
unnamed: B.19, TET36.2
unnamed: B.18, TET36.3
unnamed: B.17, TET35.0
unnamed: B.16, TET35.1
unnamed: B.15, TET35.2
unnamed: B.14, TET35.3
unnamed: B.13, TET34.0
unnamed: B.12, TET34.1
unnamed: B.11, TET34.2
unnamed: B.10, TET34.3
unnamed: B.9, TET33.0
unnamed: B.8, TET33.1
unnamed: B.7, TET33.2
unnamed: B.6, TET33.3
unnamed: B.5, TET32.0
unnamed: B.4, TET32.1
unnamed: B.3, TET32.2
unnamed: B.38, TET40.2
unnamed: B.39, TET40.1
unnamed: B.40, TET40.0
unnamed: B.41, TET41.3
unnamed: B.42, TET41.2
unnamed: B.43, TET41.1
unnamed: B.44, TET41.0
unnamed: B.45, TET42.3
unnamed: B.46, TET42.2
unnamed: B.47, TET42.1
unnamed: B.48, TET42.0
unnamed: B.49, TET43.3
unnamed: B.50, TET43.2
unnamed: B.51, TET43.1
unnamed: B.52, TET43.0
unnamed: B.53, TET44.3
unnamed: B.54, TET44.2
unnamed: B.55, TET44.1
unnamed: B.56, TET44.0
unnamed: B.57, TET45.3
unnamed: B.58, TET45.2
unnamed: B.59, TET45.1
unnamed: B.60, TET45.0
unnamed: B.61, TET46.3
unnamed: B.62, TET46.2
unnamed: B.63, TET46.1
unnamed: B.64, TET46.0
unnamed: B.65, TET47.3
unnamed: B.66, TET47.2
unnamed: B.67, TET47.1
unnamed: B.68, TET47.0
unnamed: B.2, TET32.3
unnamed: B.37, TET40.3
unnamed: C.4, TET16.2
unnamed: C.5, TET16.3
unnamed: C.6, TET17.0
unnamed: C.7, TET17.1
unnamed: C.10, TET18.0
unnamed: C.11, TET18.1
unnamed: C.14, TET19.0
unnamed: C.15, TET19.1
unnamed: C.18, TET20.0
unnamed: C.19, TET20.1
unnamed: C.22, TET21.0
unnamed: C.23, TET21.1
unnamed: C.27, TET22.1
unnamed: C.26, TET22.0
unnamed: C.30, TET23.0
unnamed: C.31, TET23.1
unnamed: C.43, TET25.2
unnamed: C.48, TET26.3
unnamed: C.47, TET26.2
unnamed: C.52, TET27.3
unnamed: C.51, TET27.2
unnamed: C.56, TET28.3
unnamed: C.55, TET28.2
unnamed: C.60, TET29.3
unnamed: C.59, TET29.2
unnamed: C.61, TET30.0
unnamed: C.63, TET30.2
unnamed: C.68, TET31.3
unnamed: C.67, TET31.2
unnamed: C.44, TET25.3
unnamed: C.39, TET24.2
unnamed: C.40, TET24.3
unnamed: A.37, TET8.3
REF_A: A.1, REF_A.P$1
REF_B: B.1, REF_B.P$1
REF_C: C.1, REF_C.P$1
REF_D: D.1, REF_D.P$1
